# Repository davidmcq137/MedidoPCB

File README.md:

# MedidoPCB
PCB for Medido Pump

This is a printed circuit board for the controller for the Medido Pump. 

License: Open Source Hardware

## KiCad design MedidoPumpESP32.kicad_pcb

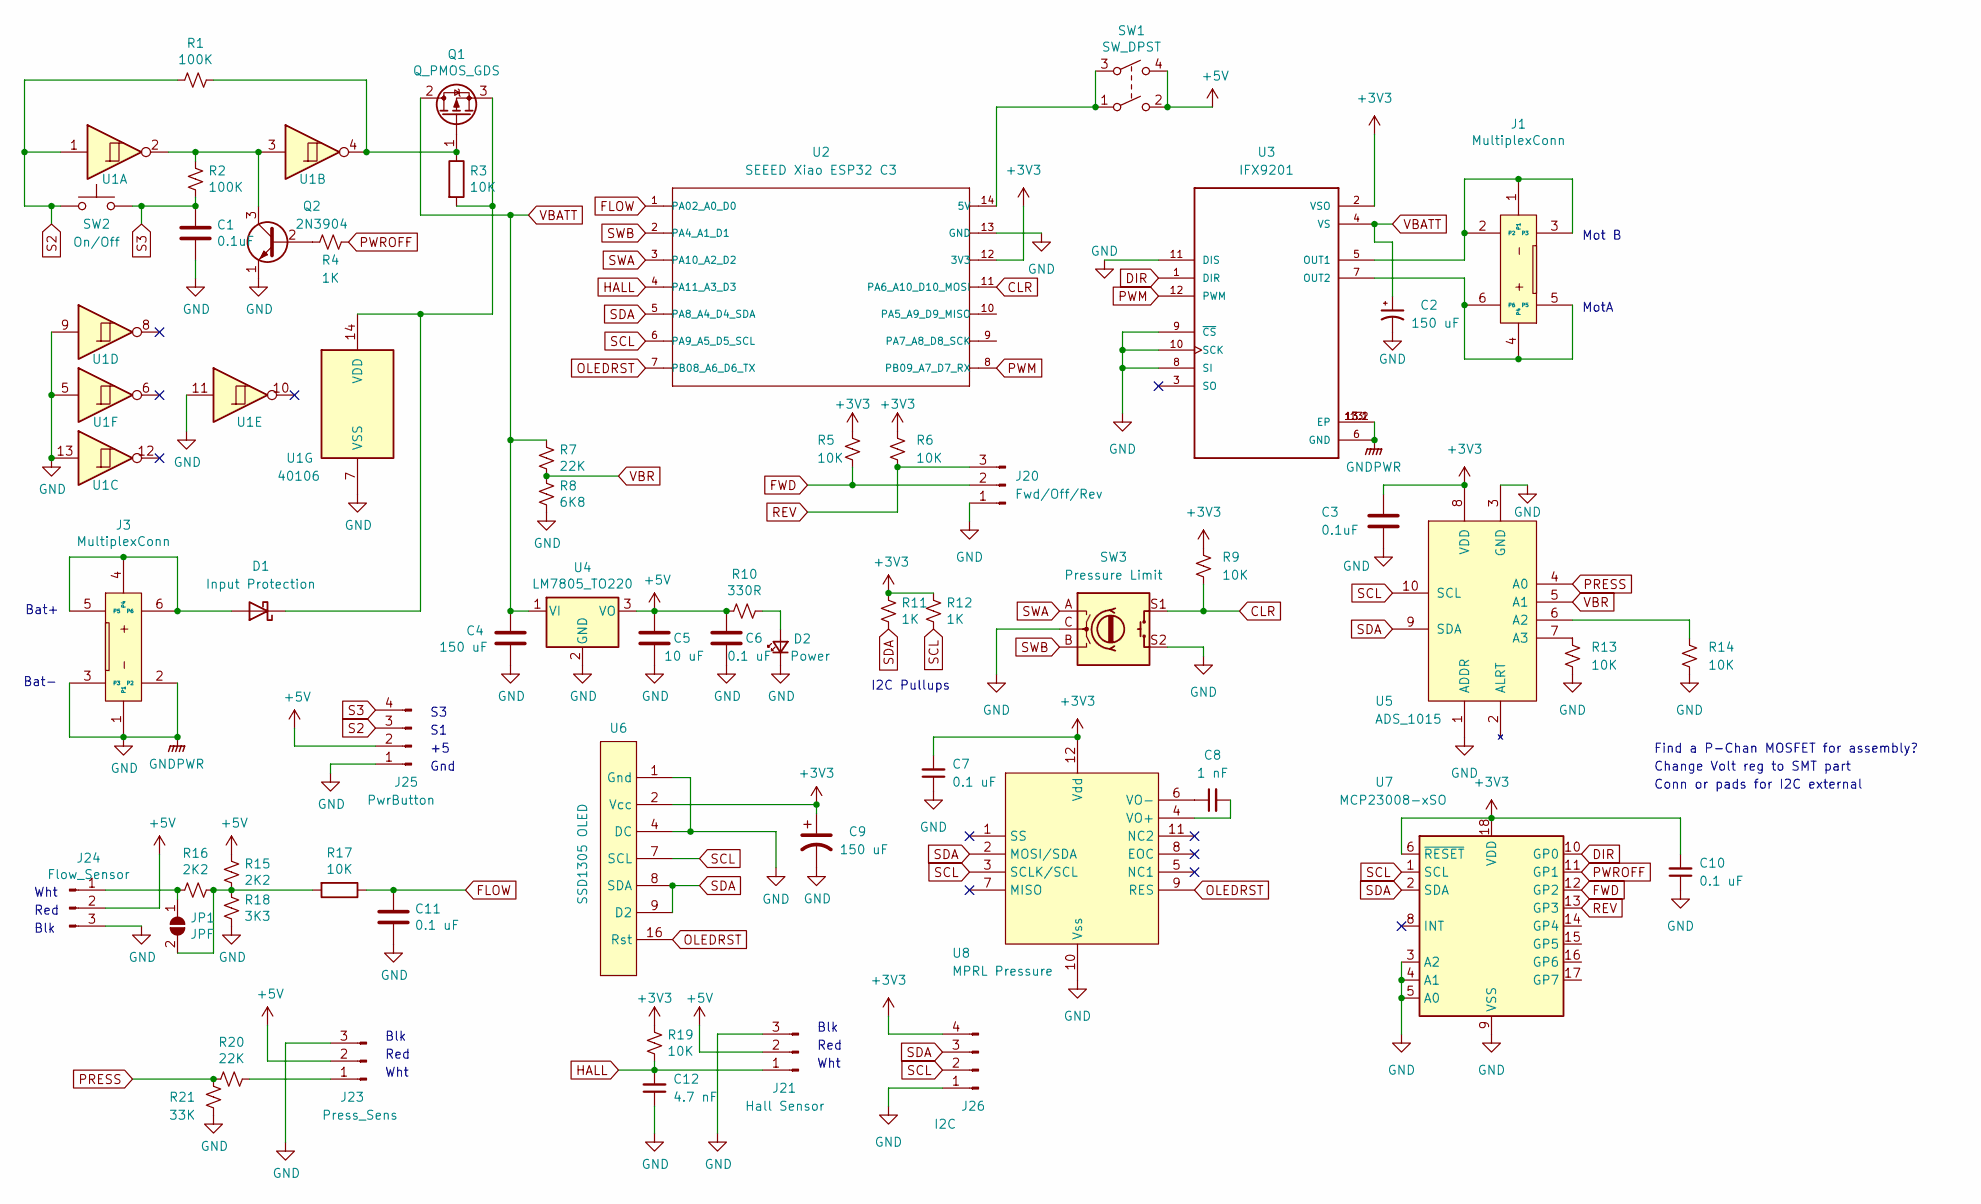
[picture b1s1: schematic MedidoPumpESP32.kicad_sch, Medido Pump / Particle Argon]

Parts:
C1, C3: 0.1uF; C_0805_2012Metric
C2, C4, C9: 150 uF; C_Elec_10x10.2
C5: 10 uF; C_Elec_10x10.2
C6, C7, C10, C11: 0.1 uF; C_0402_1005Metric
C8: 1 nF; C_0805_2012Metric
C12: 4.7 nF; C_0805_2012Metric
D1: Input Protection; D_5W_P12.70mm_Horizontal
D2: Power; LED_0805_2012Metric
J1, J3: MultiplexConn
J20: Fwd/Off/Rev; PinHeader_1x03_P2.54mm_Vertical
J21: Hall Sensor; PinHeader_1x03_P2.54mm_Vertical
J23: Press_Sens; PinHeader_1x03_P2.54mm_Vertical
J24: Flow_Sensor; PinHeader_1x03_P2.54mm_Vertical
J25: PwrButton; PinHeader_1x04_P2.54mm_Vertical
J26: I2C; PinHeader_1x04_P2.54mm_Vertical
JP1: JPF; SolderJumper-2_P1.3mm_Open_RoundedPad1.0x1.5mm
Q1: Q_PMOS_GDS; TO-220-3_Vertical
Q2: 2N3904; TO-126-3_Vertical
R1, R2: 100K; R_0805_2012Metric
R3, R5, R6, R9, R13, R14, R17, R19: 10K; R_0805_2012Metric
R4, R11, R12: 1K; R_0805_2012Metric
R7, R20: 22K; R_0805_2012Metric
R8: 6K8; R_0805_2012Metric
R10: 330R; R_0805_2012Metric
R15, R16: 2K2; R_0805_2012Metric
R18: 3K3; R_0805_2012Metric
R21: 33K; R_0805_2012Metric
SW1: SW_DPST; SmallSlider
SW2: On/Off; SW_PUSH_6mm
SW3: Pressure Limit; RotaryEncoder_Bourns_Vertical_PEC12R-3x17F-Sxxxx
U1: 40106; SOIC-14_3.9x8.7mm_P1.27mm; LCSC C38184
U2: SEEED Xiao ESP32 C3; SeeedS3
U3: IFX9201; CONV_IFX9201SGAUMA1
U4: LM7805_TO220; TO-220-3_Vertical
U5: ADS_1015; VSSOP-10_3x3mm_P0.5mm; LCSC C701606
U6: SSD1305 OLED; SSD1305_OLED
U7: MCP23008-xSO; SOIC-18W_7.5x11.6mm_P1.27mm; LCSC C92253
U8: MPRL Pressure; HoneywellMPRL

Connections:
+3V3: C3.1, C7.2, C9.1, C10.2, J26.4, R5.1, R6.1, R9.1, R11.1, R12.1, R19.1, U2.12 (3V3), U3.2 (VSO), U5.8 (VDD), U6.2 (Vcc), U7.6 (~RESET), U7.18 (VDD), U8.12 (Vdd)
+5V: C5.1, C6.1, J21.2, J23.2, J24.2, J25.2, R10.2, R15.1, SW1.2, SW1.4, U4.3 (VO)
CLR: R9.2, SW3.S1, U2.11 (PA6_A10_D10_MOSI)
DIR: U3.1 (DIR), U7.10 (GP0)
FLOW: C11.1, R17.1, U2.1 (PA02_A0_D0)
FWD: J20.2, R5.2, U7.12 (GP2)
GND: C1.2, C2.2, C3.2, C4.2, C5.2, C6.2, C7.1, C9.2, C10.1, C11.2, C12.1, D2.1 (K), J3.1, J3.2, J3.3, J20.1, J21.3, J23.3, J24.3, J25.1, J26.1, Q2.1 (E), R8.2, R13.2, R14.2, R18.2, R21.2, SW3.C, SW3.S2, U1.5, U1.7 (VSS), U1.9, U1.11, U1.13, U2.13 (GND), U3.6 (GND), U3.8 (SI), U3.9 (~CS), U3.10 (SCK), U3.11 (DIS), U3.13 (EP), U3.13.1 (EP), U3.13.2 (EP), U4.2 (GND), U5.1 (ADDR), U5.3 (GND), U6.1 (Gnd), U6.4 (DC), U7.3 (A2), U7.4 (A1), U7.5 (A0), U7.9 (VSS), U8.10 (Vss)
HALL: C12.2, J21.1, R19.2, U2.4 (PA11_A3_D3)
unnamed: D1.2 (A), J3.4, J3.5, J3.6
unnamed: D1.1 (K), Q1.3 (S), R3.2, U1.14 (VDD)
unnamed: D2.2 (A), R10.1
unnamed: J1.1, J1.2, J1.3, U3.5 (OUT1)
unnamed: J1.4, J1.5, J1.6, U3.7 (OUT2)
unnamed: J23.1, R20.1
unnamed: J24.1, JP1.1 (A), R16.2
unnamed: JP1.2 (B), R15.2, R16.1, R17.2, R18.1
unnamed: Q1.1 (G), R1.1, R3.1, U1.4
unnamed: Q2.2 (B), R4.1
unnamed: Q2.3 (C), R2.1, U1.2, U1.3
unnamed: SW1.1, SW1.3, U2.14 (5V)
unnamed: R14.1, U5.6 (A2)
unnamed: R13.1, U5.7 (A3)
unnamed: C8.2, U8.4 (VO+)
unnamed: C8.1, U8.6 (VO-)
OLEDRST: U2.7 (PB08_A6_D6_TX), U6.16 (Rst), U8.9 (RES)
PRESS: R20.2, R21.1, U5.4 (A0)
PWM: U2.8 (PB09_A7_D7_RX), U3.12 (PWM)
PWROFF: R4.2, U7.11 (GP1)
REV: J20.3, R6.2, U7.13 (GP3)
S2: J25.3, R1.2, SW2.1, U1.1
S3: C1.1, J25.4, R2.2, SW2.2
SCL: J26.2, R12.2, U2.6 (PA9_A5_D5_SCL), U5.10 (SCL), U6.7 (SCL), U7.1 (SCL), U8.3 (SCLK/SCL)
SDA: J26.3, R11.2, U2.5 (PA8_A4_D4_SDA), U5.9 (SDA), U6.8 (SDA), U6.9 (D2), U7.2 (SDA), U8.2 (MOSI/SDA)
SWA: SW3.A, U2.3 (PA10_A2_D2)
SWB: SW3.B, U2.2 (PA4_A1_D1)
VBATT: C2.1, C4.1, Q1.2 (D), R7.1, U3.4 (VS), U4.1 (VI)
VBR: R7.2, R8.1, U5.5 (A1)

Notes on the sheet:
I2C Pullups
Bat+
Find a P-Chan MOSFET for assembly?
Change Volt reg to SMT part
Gnd
Red
MotA
Conn or pads for I2C external
Blk
Wht
Bat-
Mot B

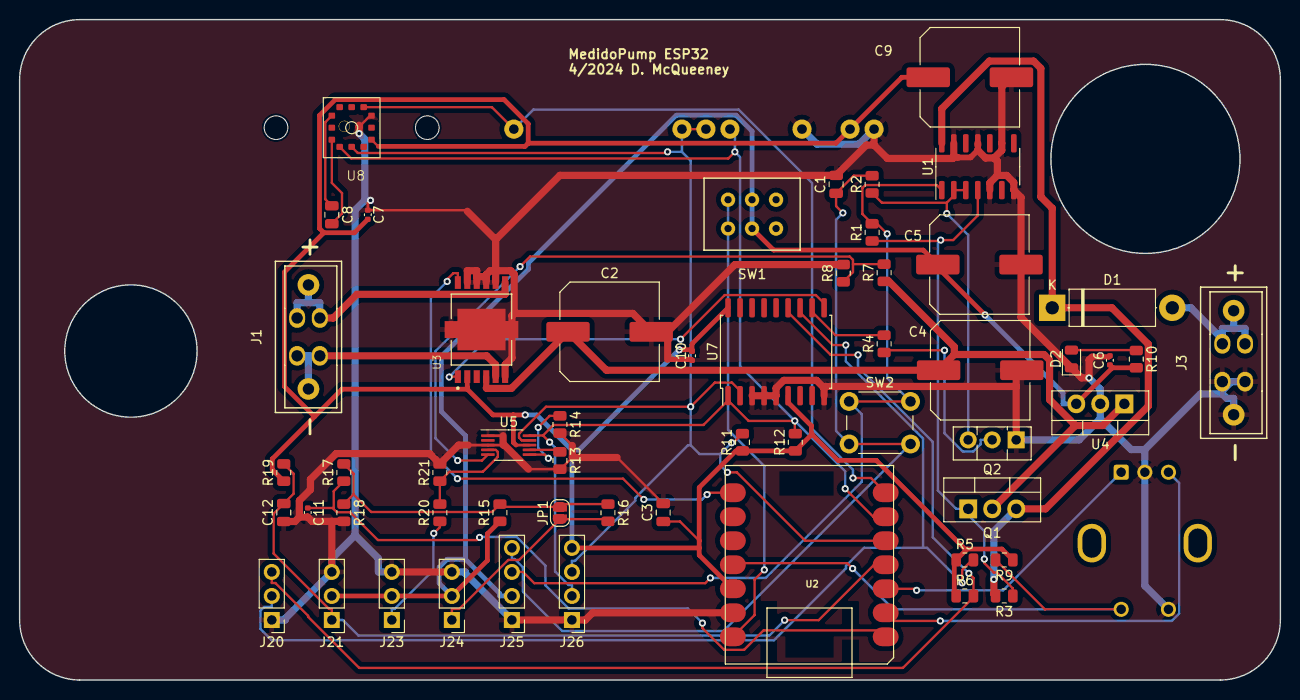
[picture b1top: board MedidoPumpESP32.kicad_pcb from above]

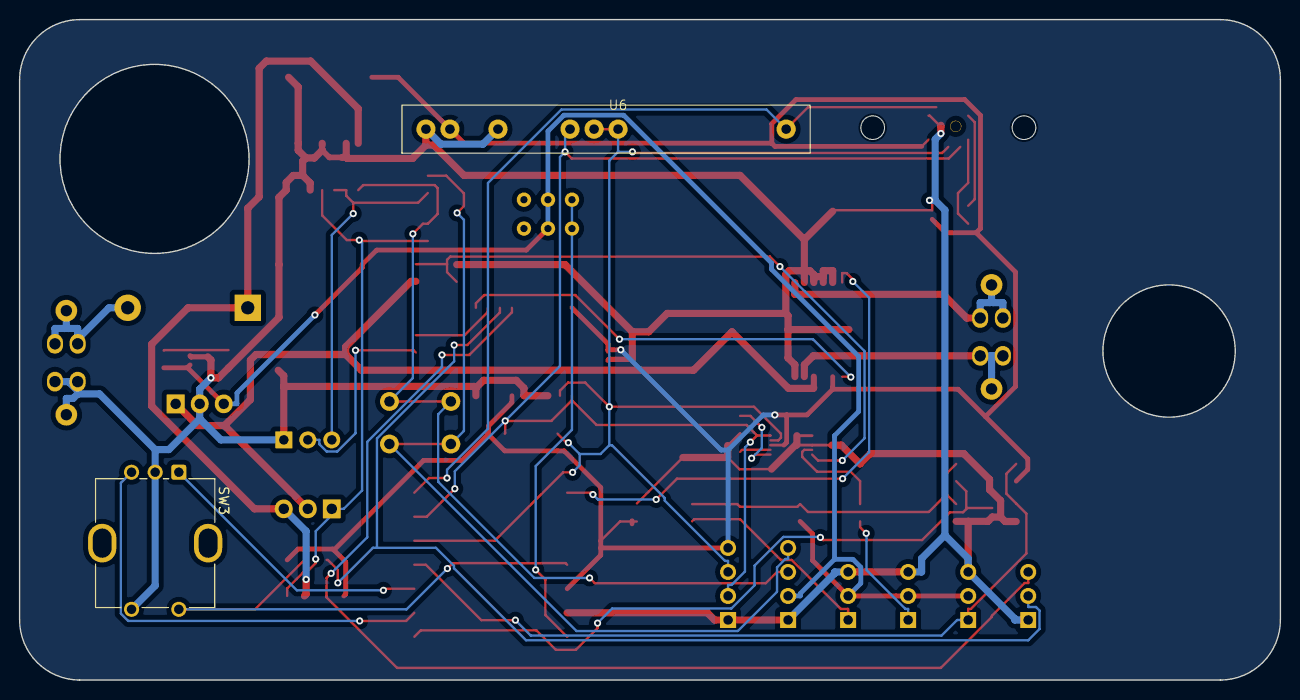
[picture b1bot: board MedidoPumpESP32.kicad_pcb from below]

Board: 2 copper layers, 133.4 x 69.8 mm, 57 parts (2 on the bottom side), 37 nets.

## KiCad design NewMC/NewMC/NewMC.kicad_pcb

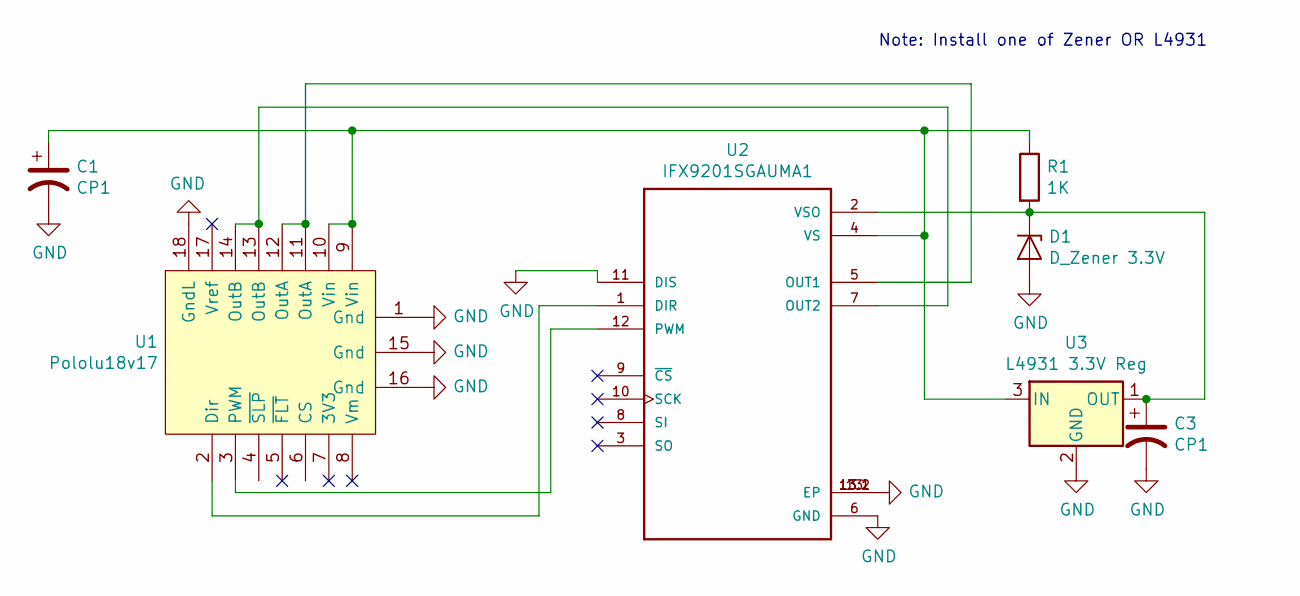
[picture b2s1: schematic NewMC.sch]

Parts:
C1, C3: CP1; CP_Radial_D6.3mm_P2.50mm
D1: D_Zener 3.3V; D_DO-41_SOD81_P2.54mm_Vertical_KathodeUp
R1: 1K; R_Axial_DIN0207_L6.3mm_D2.5mm_P2.54mm_Vertical
U1: Pololu18v17; Pololu18V17
U2: IFX9201SGAUMA1; CONV_IFX9201SGAUMA1
U3: L4931 3.3V Reg; TO-92_Inline

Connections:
GND: C1.2, C3.2, D1.2 (A), U1.1 (Gnd), U1.15 (Gnd), U1.16 (Gnd), U1.18 (GndL), U2.6 (GND), U2.11 (DIS), U2.13 (EP), U2.13.1 (EP), U2.13.2 (EP), U3.2 (GND)
unnamed: C1.1, R1.1, U1.9 (Vin), U1.10 (Vin), U2.4 (VS), U3.3 (IN)
unnamed: C3.1, D1.1 (K), R1.2, U2.2 (VSO), U3.1 (OUT)
unnamed: U1.2 (Dir), U2.1 (DIR)
unnamed: U1.3 (PWM), U2.12 (PWM)
unnamed: U1.11 (OutA), U1.12 (OutA), U2.5 (OUT1)
unnamed: U1.13 (OutB), U1.14 (OutB), U2.7 (OUT2)

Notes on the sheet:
Note: Install one of Zener OR L4931

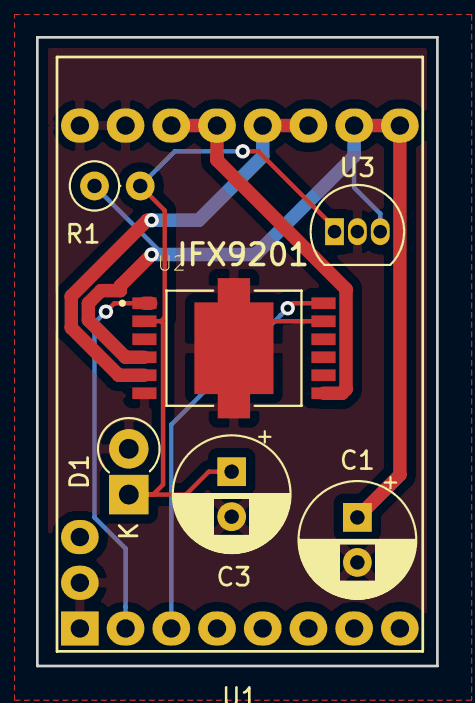
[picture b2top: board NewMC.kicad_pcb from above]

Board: 2 copper layers, 22.2 x 34.9 mm, 7 parts (0 on the bottom side), 7 nets.

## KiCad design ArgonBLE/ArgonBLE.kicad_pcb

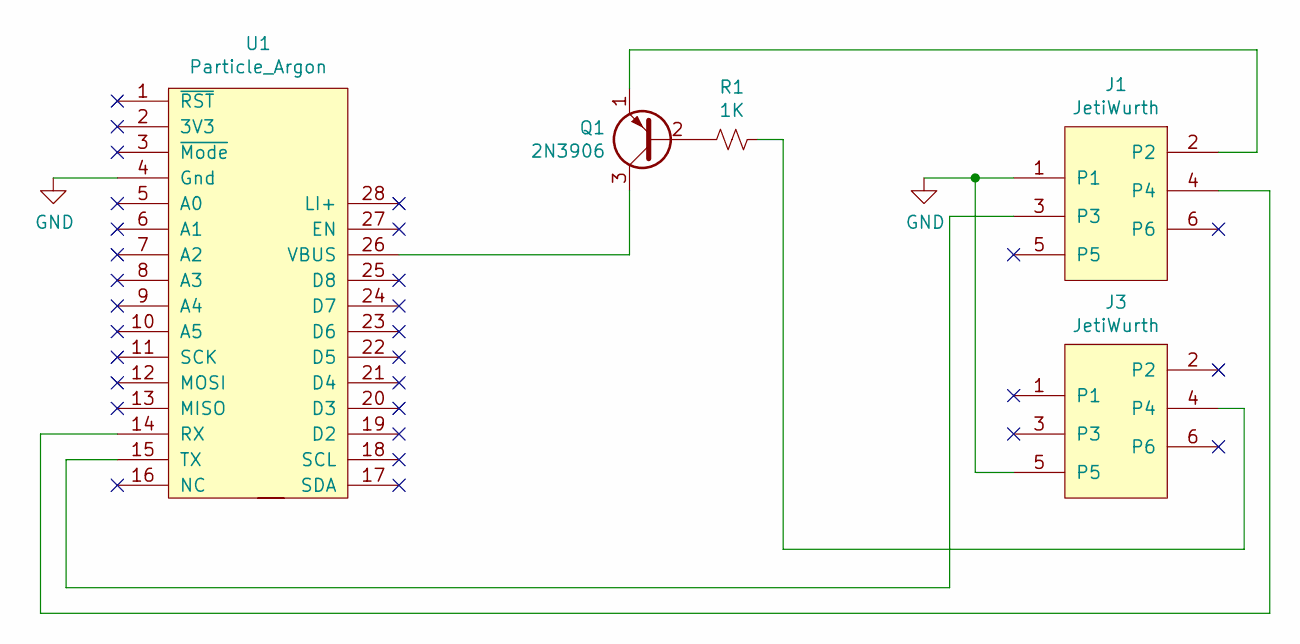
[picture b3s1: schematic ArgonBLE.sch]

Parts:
J1, J3: JetiWurth
Q1: 2N3906; TO-92_HandSolder
R1: 1K; R_Axial_DIN0207_L6.3mm_D2.5mm_P10.16mm_Horizontal
U1: Particle_Argon

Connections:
GND: J1.1, J3.5, U1.4 (Gnd)
unnamed: J1.2, Q1.1 (E)
unnamed: J1.3, U1.15 (TX)
unnamed: J1.4, U1.14 (RX)
unnamed: J3.4, R1.1
unnamed: Q1.2 (B), R1.2
unnamed: Q1.3 (C), U1.26 (VBUS)

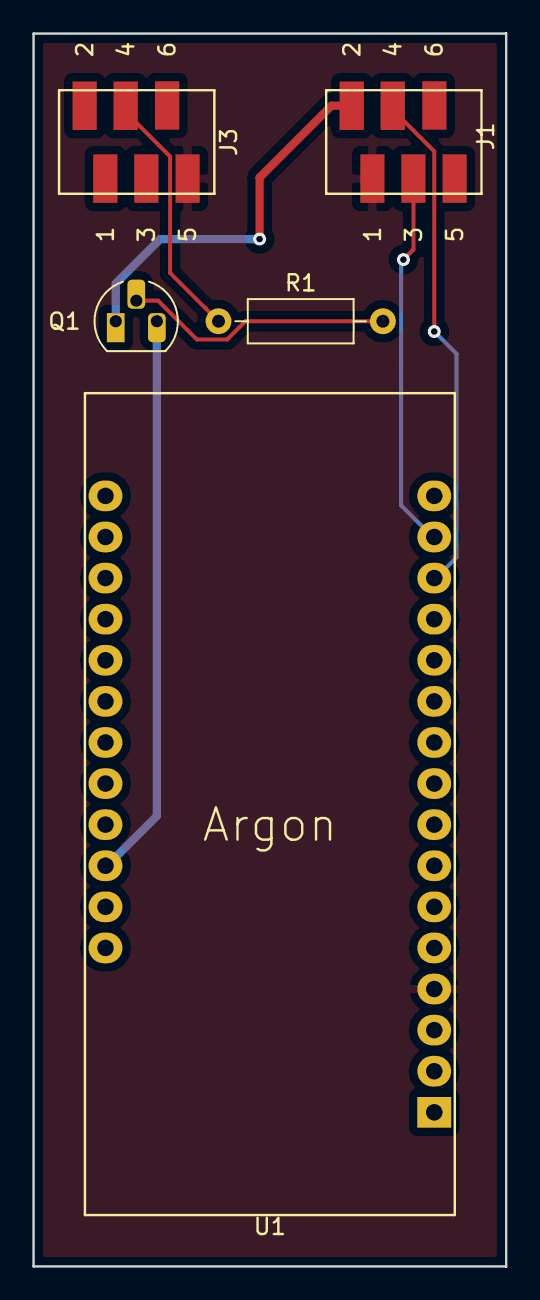
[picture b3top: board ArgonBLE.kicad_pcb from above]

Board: 2 copper layers, 29.2 x 76.2 mm, 5 parts (0 on the bottom side), 7 nets.

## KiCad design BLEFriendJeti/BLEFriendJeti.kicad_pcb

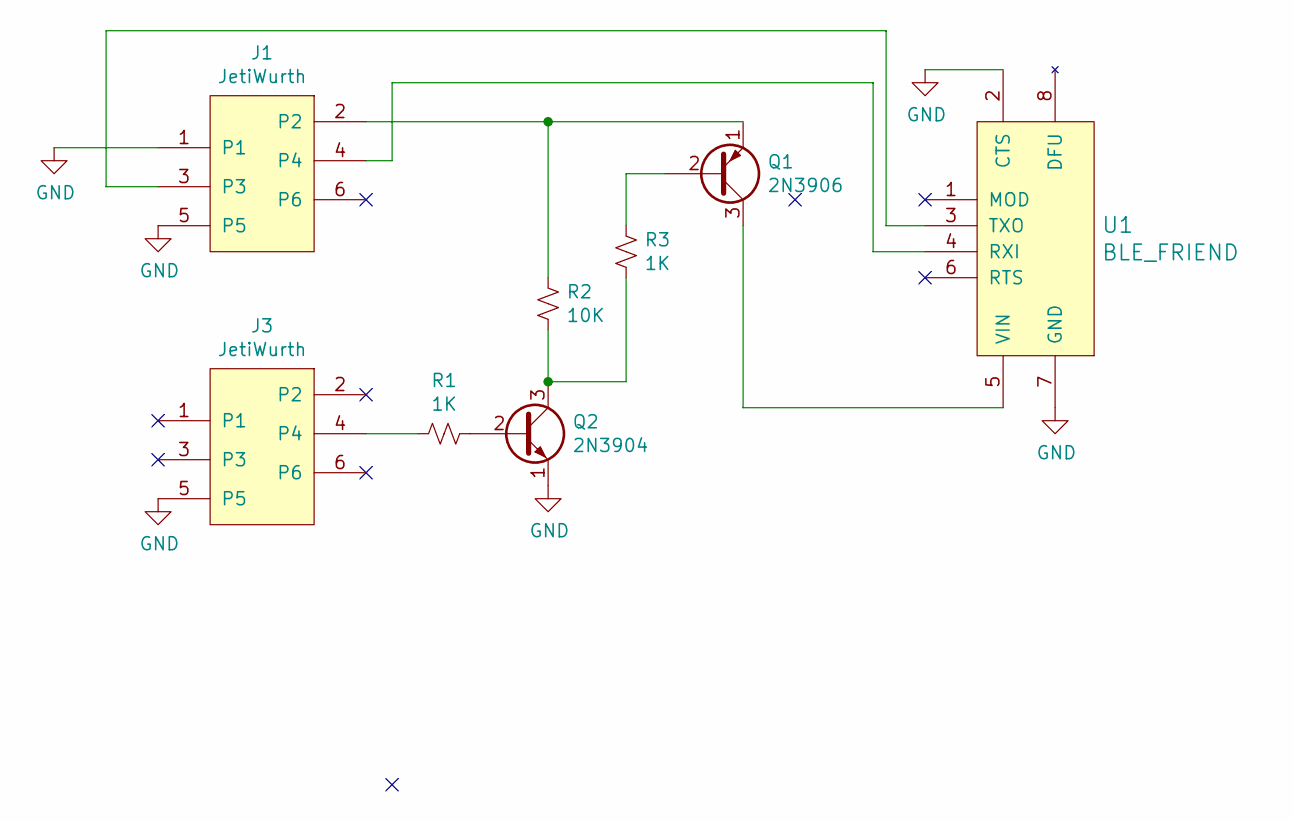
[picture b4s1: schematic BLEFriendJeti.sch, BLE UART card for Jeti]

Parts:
J1, J3: JetiWurth
Q1: 2N3906; TO-92L_HandSolder
Q2: 2N3904; TO-92L_HandSolder
R1, R3: 1K; R_Axial_DIN0207_L6.3mm_D2.5mm_P7.62mm_Horizontal
R2: 10K; R_Axial_DIN0207_L6.3mm_D2.5mm_P7.62mm_Horizontal
U1: BLE_FRIEND

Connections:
GND: J1.1, J1.5, J3.5, Q2.1 (E), U1.2 (CTS), U1.7 (GND)
unnamed: J1.2, Q1.1 (E), R2.1
unnamed: J1.3, U1.3 (TXO)
unnamed: J1.4, U1.4 (RXI)
unnamed: J3.4, R1.1
unnamed: Q1.2 (B), R3.1
unnamed: Q1.3 (C), U1.5 (VIN)
unnamed: Q2.2 (B), R1.2
unnamed: Q2.3 (C), R2.2, R3.2

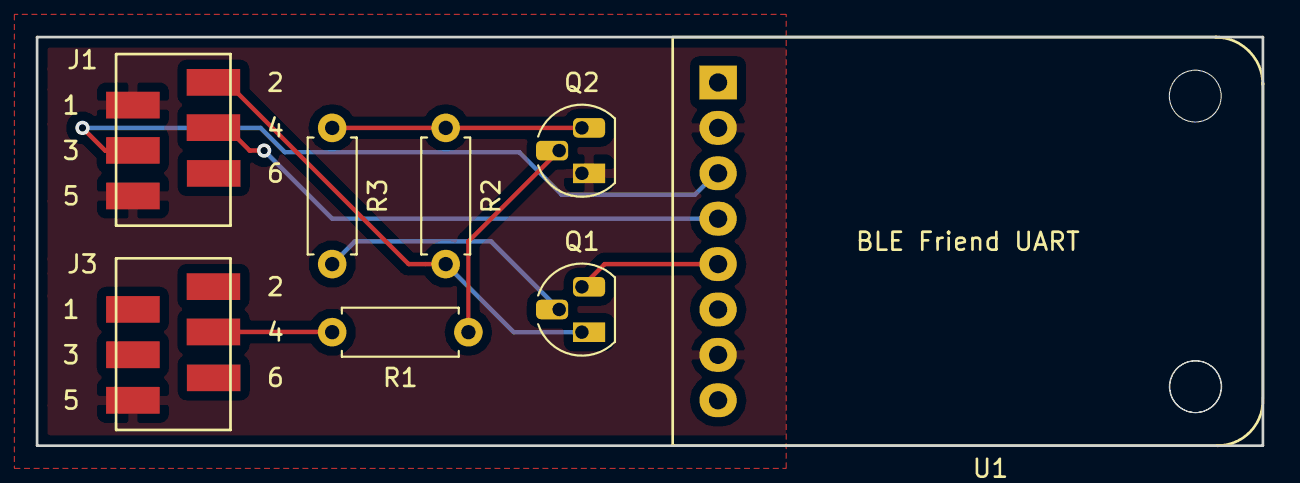
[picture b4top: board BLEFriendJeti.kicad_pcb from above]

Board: 2 copper layers, 68.6 x 22.9 mm, 8 parts (0 on the bottom side), 9 nets.

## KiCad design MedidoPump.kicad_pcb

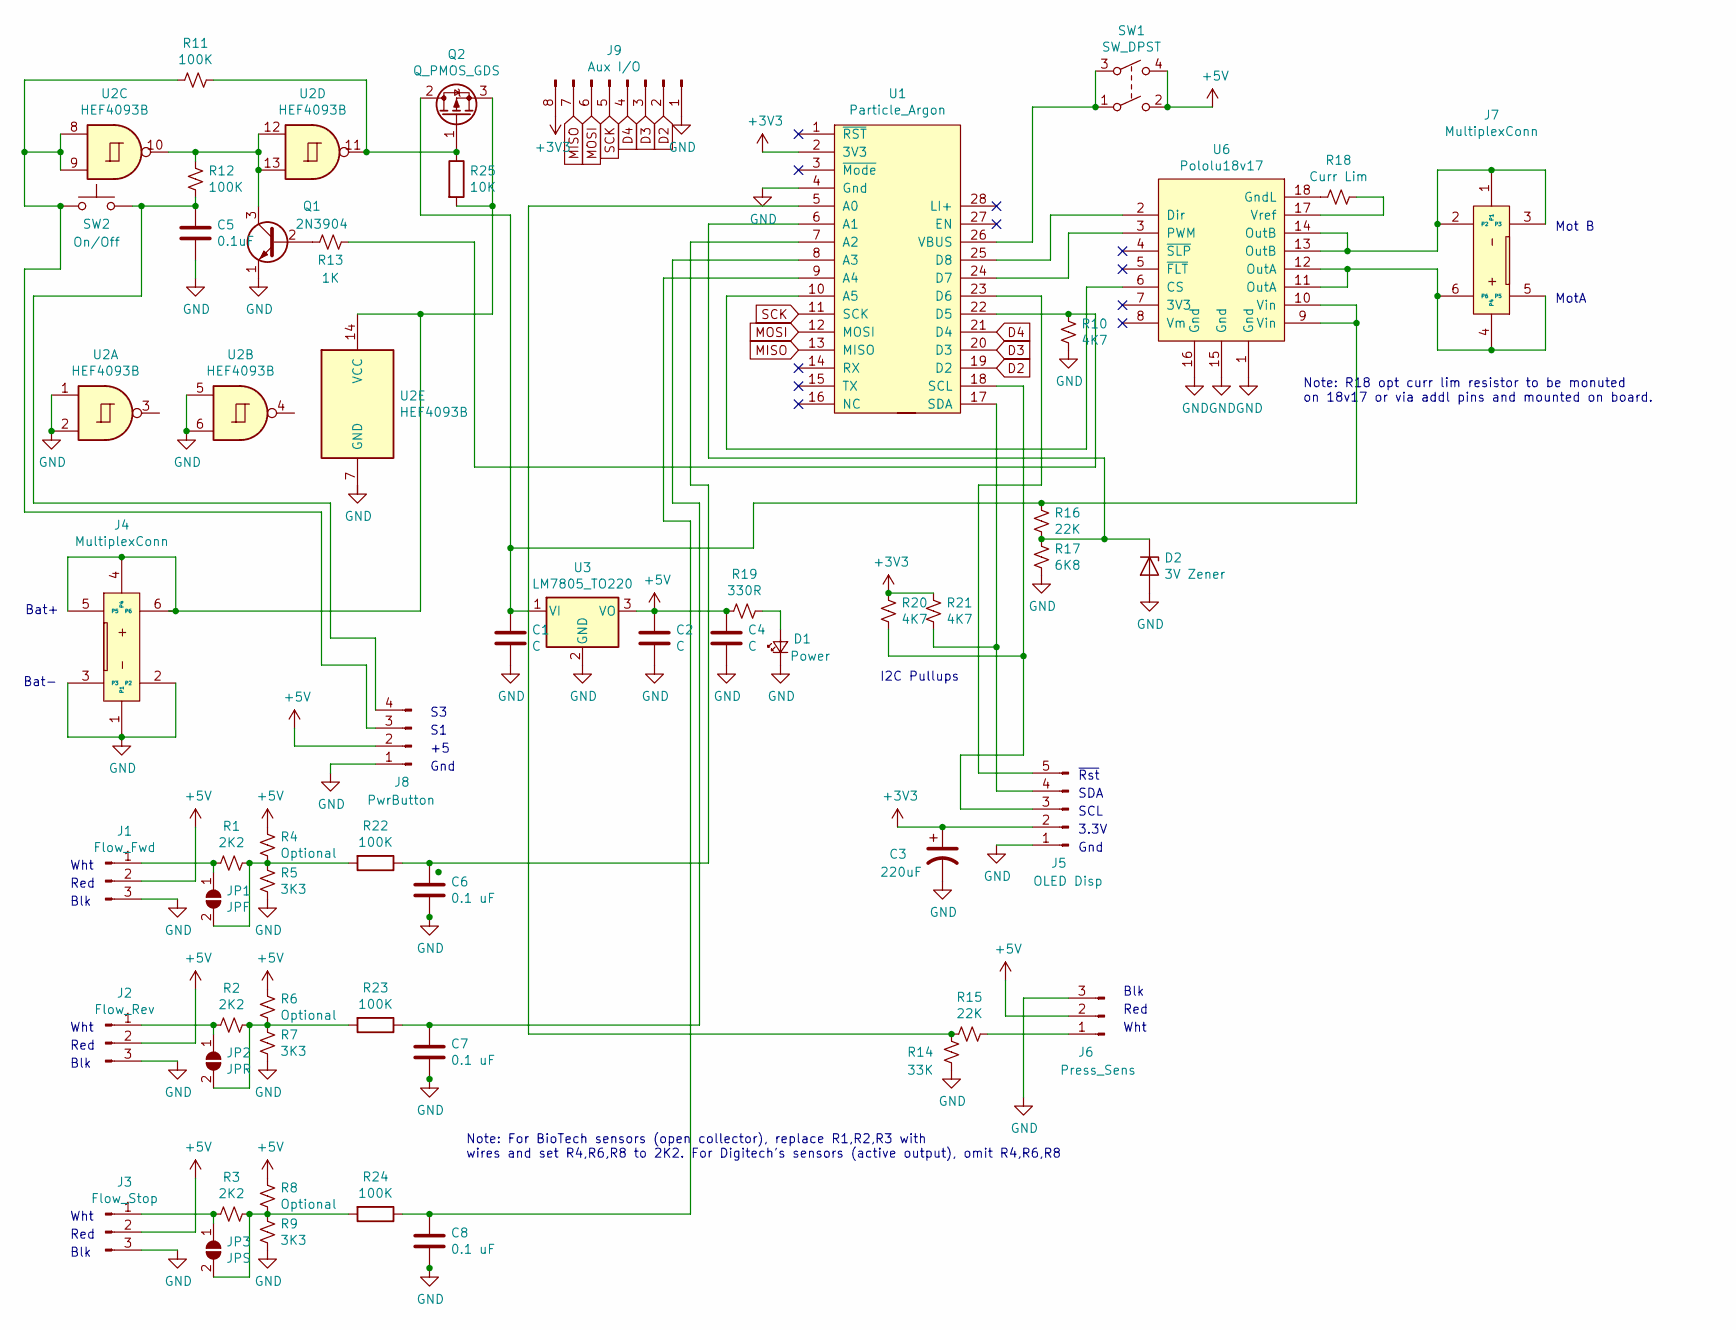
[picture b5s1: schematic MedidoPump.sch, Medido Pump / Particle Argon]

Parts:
C1, C2: C; CP_Radial_D7.5mm_P2.50mm
C3: 220uF; CP_Radial_D10.0mm_P5.00mm
C4: C; C_Disc_D12.0mm_W4.4mm_P7.75mm
C5: 0.1uF; C_Disc_D12.0mm_W4.4mm_P7.75mm
C6, C7, C8: 0.1 uF; C_Disc_D12.0mm_W4.4mm_P7.75mm
D1: Power; LED_D3.0mm
D2: 3V Zener; D_5W_P10.16mm_Horizontal
J1: Flow_Fwd; PinHeader_1x03_P2.54mm_Vertical
J2: Flow_Rev; PinHeader_1x03_P2.54mm_Vertical
J3: Flow_Stop; PinHeader_1x03_P2.54mm_Vertical
J4, J7: MultiplexConn
J5: OLED Disp; PinHeader_1x05_P2.54mm_Vertical
J6: Press_Sens; PinHeader_1x03_P2.54mm_Vertical
J8: PwrButton; PinHeader_1x04_P2.54mm_Vertical
J9: Aux I/O; PinHeader_1x08_P2.54mm_Vertical
JP1: JPF; SolderJumper-2_P1.3mm_Open_RoundedPad1.0x1.5mm
JP2: JPR; SolderJumper-2_P1.3mm_Open_RoundedPad1.0x1.5mm
JP3: JPS; SolderJumper-2_P1.3mm_Open_RoundedPad1.0x1.5mm
Q1: 2N3904; TO-126-3_Vertical
Q2: Q_PMOS_GDS; TO-220-3_Vertical
R1, R2, R3: 2K2; R_Axial_DIN0207_L6.3mm_D2.5mm_P10.16mm_Horizontal
R4, R6, R8: Optional; R_Axial_DIN0207_L6.3mm_D2.5mm_P10.16mm_Horizontal
R5, R7, R9: 3K3; R_Axial_DIN0207_L6.3mm_D2.5mm_P10.16mm_Horizontal
R10, R20, R21: 4K7; R_Axial_DIN0207_L6.3mm_D2.5mm_P10.16mm_Horizontal
R11, R12, R22, R23, R24: 100K; R_Axial_DIN0207_L6.3mm_D2.5mm_P10.16mm_Horizontal
R13: 1K; R_Axial_DIN0207_L6.3mm_D2.5mm_P10.16mm_Horizontal
R14: 33K; R_Axial_DIN0207_L6.3mm_D2.5mm_P10.16mm_Horizontal
R15, R16: 22K; R_Axial_DIN0207_L6.3mm_D2.5mm_P10.16mm_Horizontal
R17: 6K8; R_Axial_DIN0207_L6.3mm_D2.5mm_P10.16mm_Horizontal
R18: Curr Lim; R_Axial_DIN0207_L6.3mm_D2.5mm_P10.16mm_Horizontal
R19: 330R; R_Axial_DIN0207_L6.3mm_D2.5mm_P10.16mm_Horizontal
R25: 10K; R_Axial_DIN0207_L6.3mm_D2.5mm_P10.16mm_Horizontal
SW1: SW_DPST; SmallSlider
SW2: On/Off; SW_PUSH_6mm
U1: Particle_Argon
U2: HEF4093B; DIP-14_W7.62mm
U3: LM7805_TO220; TO-220-3_Vertical
U6: Pololu18v17; Pololu18V17

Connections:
+3V3: C3.1, J5.2, J9.8, R20.1, R21.1, U1.2 (3V3)
+5V: C2.1, C4.1, J1.2, J2.2, J3.2, J6.2, J8.2, R4.1, R6.1, R8.1, R19.2, SW1.2, SW1.4, U3.3 (VO)
D2: J9.2, U1.19 (D2)
D3: J9.3, U1.20 (D3)
D4: J9.4, U1.21 (D4)
GND: C1.2, C2.2, C3.2, C4.2, C5.2, C6.2, C7.2, C8.2, D1.1 (K), D2.2 (A), J1.3, J2.3, J3.3, J4.1, J4.2, J4.3, J5.1, J6.3, J8.1, J9.1, Q1.1 (E), R5.2, R7.2, R9.2, R10.2, R14.2, R17.2, U1.4 (Gnd), U2.1, U2.2, U2.5, U2.6, U3.2 (GND), U6.1 (Gnd), U6.15 (Gnd), U6.16 (Gnd)
MISO: J9.7, U1.13 (MISO)
MOSI: J9.6, U1.12 (MOSI)
unnamed: C1.1, Q2.2 (D), R16.1, U3.1 (VI), U6.9 (Vin), U6.10 (Vin)
unnamed: C5.1, J8.4, R12.2, SW2.2
unnamed: C6.1, R22.1, U1.7 (A2)
unnamed: C7.1, R23.1, U1.8 (A3)
unnamed: C8.1, R24.1, U1.9 (A4)
unnamed: D1.2 (A), R19.1
unnamed: D2.1 (K), R16.2, R17.1, U1.6 (A1)
unnamed: J1.1, JP1.1 (A), R1.2
unnamed: J2.1, JP2.1 (A), R2.2
unnamed: J3.1, JP3.1 (A), R3.2
unnamed: J4.4, J4.5, J4.6, Q2.3 (S), R25.2, U2.14 (VCC)
unnamed: J5.3, R20.2, U1.18 (SCL)
unnamed: J5.4, R21.2, U1.17 (SDA)
unnamed: J5.5, U1.23 (D6)
unnamed: J6.1, R15.1
unnamed: J7.1, J7.2, J7.3, U6.13 (OutB), U6.14 (OutB)
unnamed: J7.4, J7.5, J7.6, U6.11 (OutA), U6.12 (OutA)
unnamed: J8.3, R11.2, SW2.1, U2.8, U2.9
unnamed: JP1.2 (B), R1.1, R4.2, R5.1, R22.2
unnamed: JP2.2 (B), R2.1, R6.2, R7.1, R23.2
unnamed: JP3.2 (B), R3.1, R8.2, R9.1, R24.2
unnamed: Q1.2 (B), R13.1
unnamed: Q1.3 (C), R12.1, U2.10, U2.12, U2.13
unnamed: Q2.1 (G), R11.1, R25.1, U2.11
unnamed: R10.1, R13.2, U1.22 (D5)
unnamed: R14.1, R15.2, U1.5 (A0)
unnamed: R18.1, U6.17 (Vref)
unnamed: R18.2, U6.18 (GndL)
unnamed: SW1.1, SW1.3, U1.26 (VBUS)
unnamed: U1.10 (A5), U6.6 (CS)
unnamed: U1.24 (D7), U6.3 (PWM)
unnamed: U1.25 (D8), U6.2 (Dir)
SCK: J9.5, U1.11 (SCK)

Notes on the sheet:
Bat+
Bat-
Blk
Red
Wht
SCL
SDA
~Rst
3.3V
Gnd
Mot B
MotA
Note: For BioTech sensors (open collector), replace R1,R2,R3 with wires and set R4,R6,R8 to 2K2. For Digitech's sensors (active output), omit R4,R6,R8
Note: R18 opt curr lim resistor to be monuted on 18v17 or via addl pins and mounted on board.
I2C Pullups

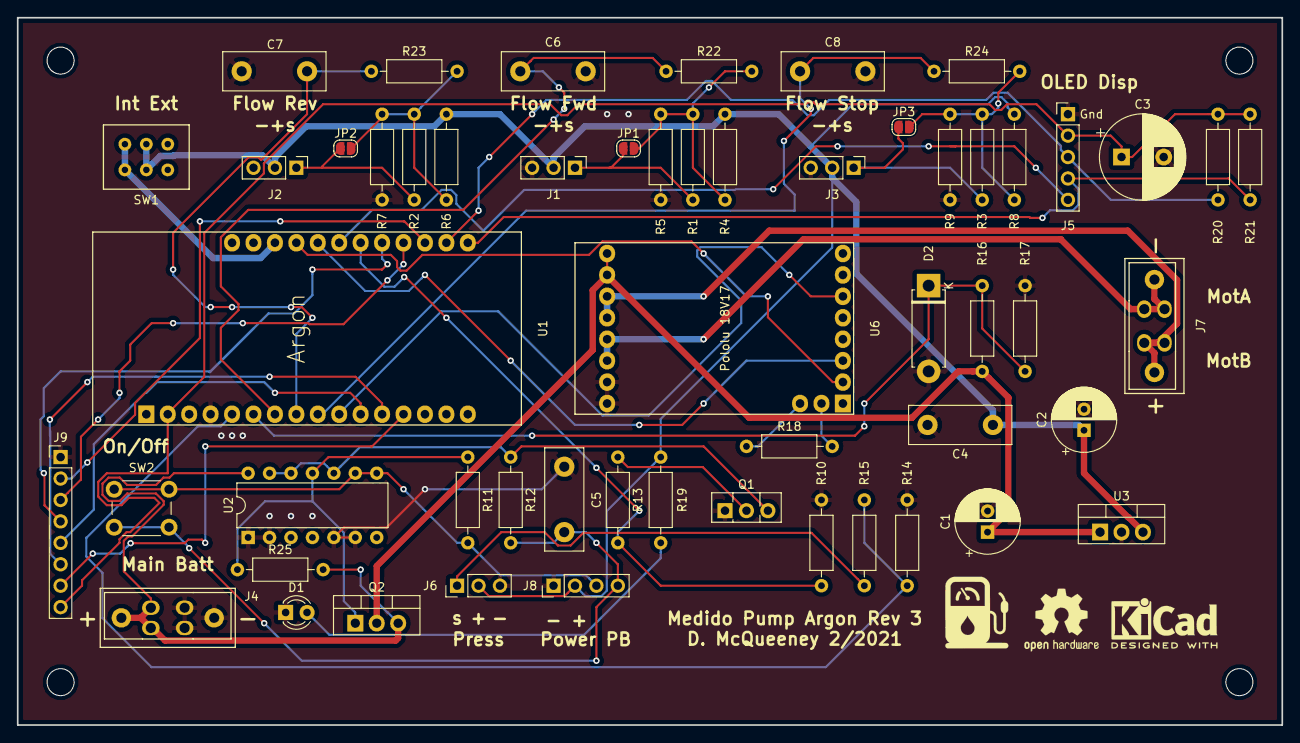
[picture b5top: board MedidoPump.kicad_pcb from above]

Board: 2 copper layers, 149.9 x 83.8 mm, 55 parts (0 on the bottom side), 41 nets.

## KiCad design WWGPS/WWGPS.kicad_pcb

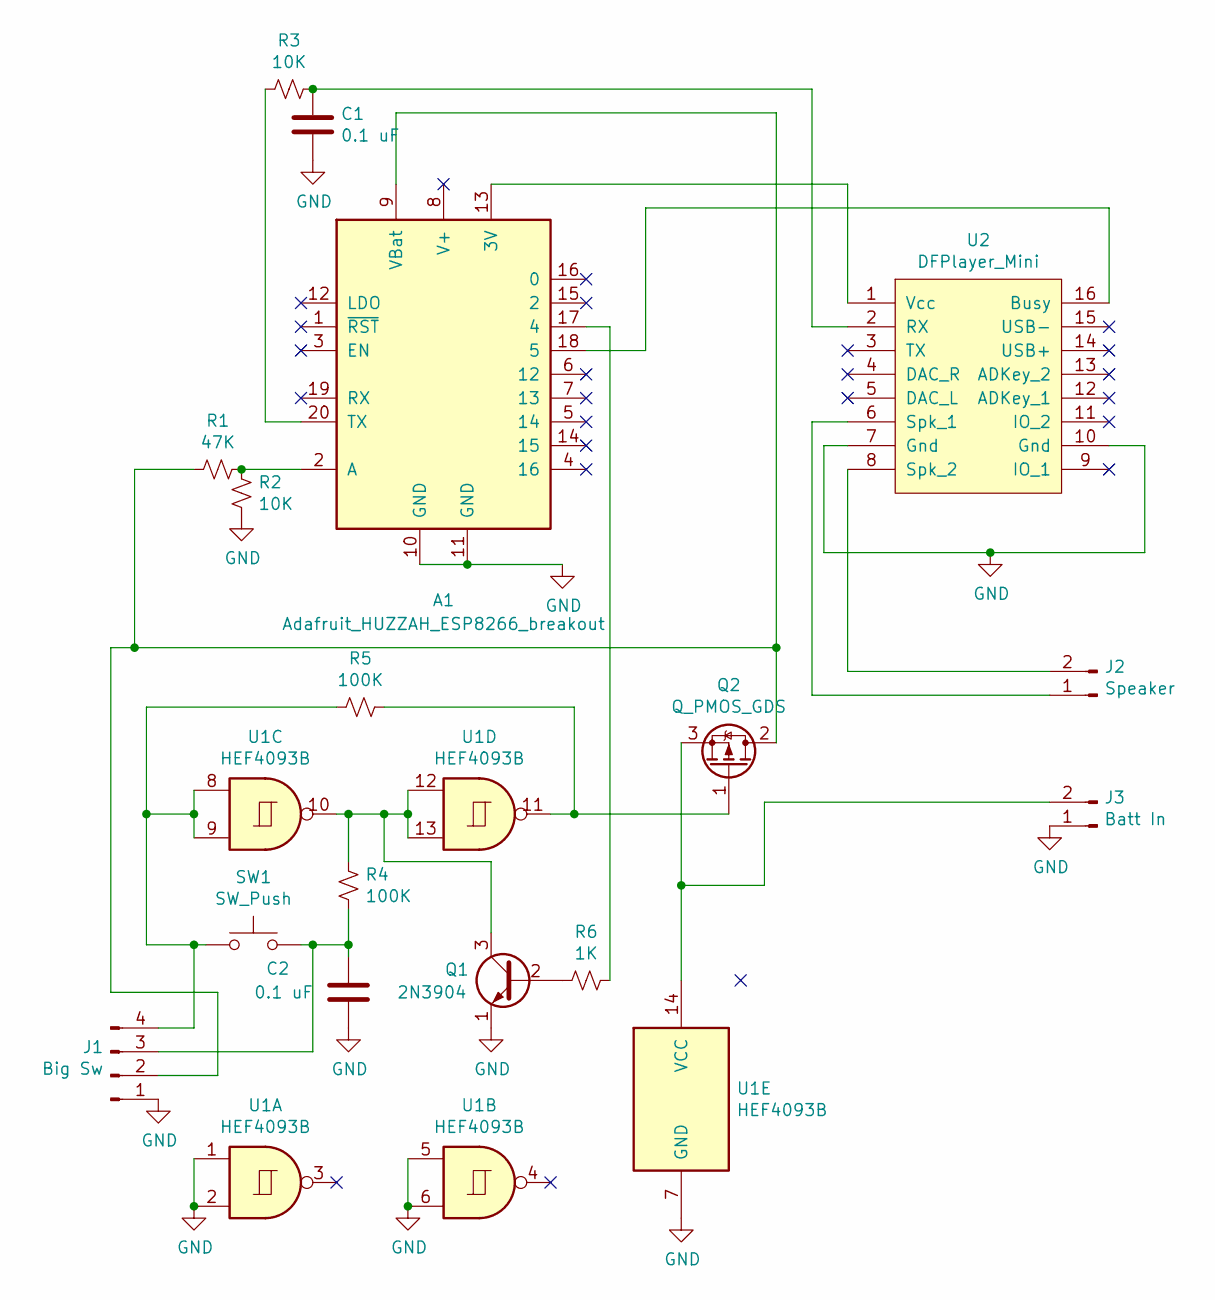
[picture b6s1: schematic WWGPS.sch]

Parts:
A1: Adafruit_HUZZAH_ESP8266_breakout
C1, C2: 0.1 uF; C_Disc_D12.0mm_W4.4mm_P7.75mm
J1: Big Sw; PinHeader_1x04_P2.54mm_Vertical
J2: Speaker; PinHeader_1x02_P2.54mm_Vertical
J3: Batt In; PinHeader_1x02_P2.54mm_Vertical
Q1: 2N3904; TO-126-3_Vertical
Q2: Q_PMOS_GDS; TO-220-3_Vertical
R1: 47K; R_Axial_DIN0207_L6.3mm_D2.5mm_P10.16mm_Horizontal
R2, R3: 10K; R_Axial_DIN0207_L6.3mm_D2.5mm_P10.16mm_Horizontal
R4, R5: 100K; R_Axial_DIN0207_L6.3mm_D2.5mm_P10.16mm_Horizontal
R6: 1K; R_Axial_DIN0207_L6.3mm_D2.5mm_P10.16mm_Horizontal
SW1: SW_Push; SW_PUSH_6mm
U1: HEF4093B; DIP-14_W7.62mm
U2: DFPlayer_Mini; dfmini

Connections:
GND: A1.10 (GND), A1.11 (GND), C1.2, C2.2, J1.1, J3.1, Q1.1 (E), R2.2, U1.1, U1.2, U1.5, U1.6, U1.7 (GND), U2.7 (Gnd), U2.10 (Gnd)
unnamed: A1.2 (A), R1.1, R2.1
unnamed: A1.9 (VBat), J1.2, Q2.2 (D), R1.2
unnamed: A1.13 (3V), U2.1 (Vcc)
unnamed: A1.17 (4), R6.1
unnamed: A1.18 (5), U2.16 (Busy)
unnamed: A1.20 (TX), R3.2
unnamed: C1.1, R3.1, U2.2 (RX)
unnamed: C2.1, J1.3, R4.2, SW1.2
unnamed: J1.4, R5.2, SW1.1, U1.8, U1.9
unnamed: J2.1, U2.6 (Spk_1)
unnamed: J2.2, U2.8 (Spk_2)
unnamed: J3.2, Q2.3 (S), U1.14 (VCC)
unnamed: Q1.2 (B), R6.2
unnamed: Q1.3 (C), R4.1, U1.10, U1.12, U1.13
unnamed: Q2.1 (G), R5.1, U1.11

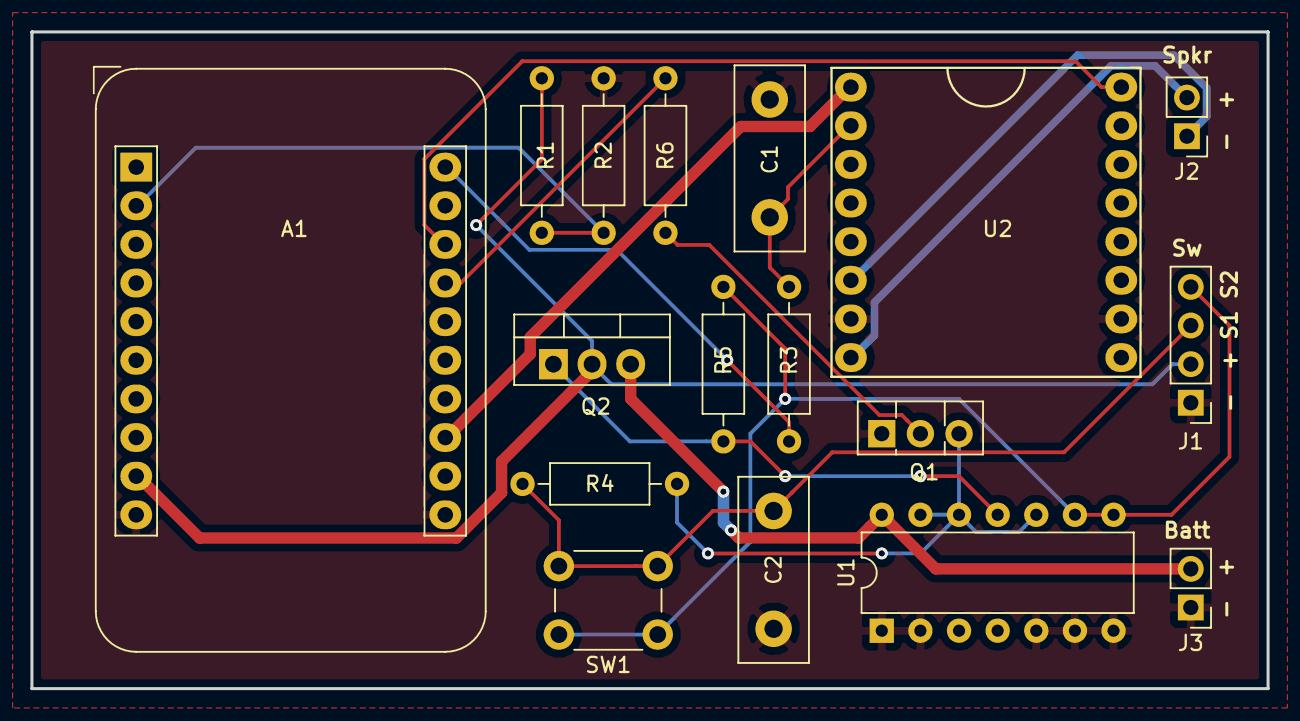
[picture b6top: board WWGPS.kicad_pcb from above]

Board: 2 copper layers, 81.3 x 43.2 mm, 17 parts (0 on the bottom side), 16 nets.

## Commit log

2020-03-20 misc
2020-03-23 shipped
